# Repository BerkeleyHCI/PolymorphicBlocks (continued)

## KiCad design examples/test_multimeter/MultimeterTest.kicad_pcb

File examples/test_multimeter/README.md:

## Revision 2

Some items were out of stock and substituted with pin compatible alternatives:

- NLAS4157 (analog switch)
  - ~TS5A3160DCKR~
  - PI5A3157 (low-end), TS5A3159 (higher-end)
- TPA2005D1 (class D audio amp)
  - ~TPA2005D1DRBQ1 (8SON / DFN package)~ also out of stock =()
  - PAM8302AASCR (note internal resistors)
- TLV9061SQDBVRQ1 (opamp)
  - ~OPA991SIDBVR~ - NOT COMPATIBLE - IT'S ACTIVE HIGH SHUTDOWN

Part selection for some generics:
- Tactile switch
  - PTS820 J25K SMTR LFS
- FFC connector alternatives that are less expensive
  - 1734592-8
  - SFV8R-1STBE1HLF

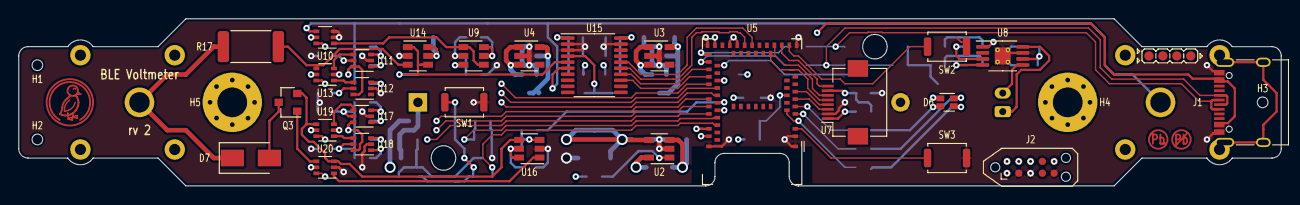
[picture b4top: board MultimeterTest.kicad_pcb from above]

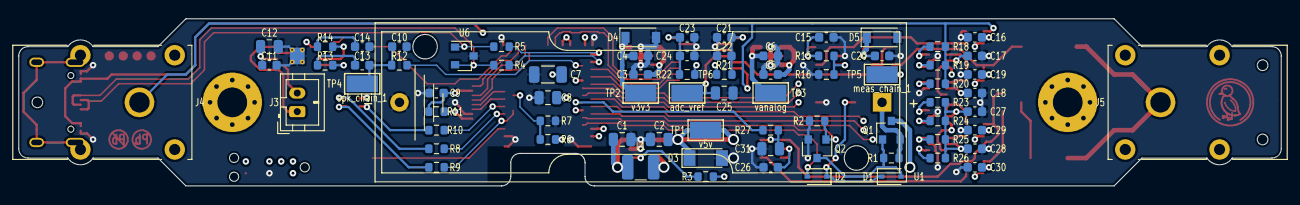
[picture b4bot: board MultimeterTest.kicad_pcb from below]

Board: 4 copper layers, 136.0 x 18.0 mm, 111 parts (76 on the bottom side), 80 nets.

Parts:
1: LeadFree; Indicator_LeadFree
2: IdDots4; Indicator_IdDots_4
C1, C8, C25: X5R 25V ±10% 10uF 0805 Multilayer Ceramic Capacit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; C_0805_2012Metric
C2, C12: 25V 4.7uF X5R ±10% 0805 Multilayer Ceramic Capaci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; C_0805_2012Metric
C3, C4, C5, C6, C9, C13, C14: 50V 1uF X5R ±10% 0603 Multilayer Ceramic Capacito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; C_0603_1608Metric
C7: 50V 10uF X5R ±10% 1206 Multilayer Ceramic Capacit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; C_1206_3216Metric
C10: 50V 47nF X7R ±10% 0603 Multilayer Ceramic Capacit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; C_0603_1608Metric
C11, C15, C16, C17, C18, C19, C20, C21, C22, C23, C24, C26, C27, C28, C29, C30: 50V 100nF X7R ±10% 0603 Multilayer Ceramic Capaci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; C_0603_1608Metric
C31: 50V 2.2uF Y5V ±20% 0805 Multilayer Ceramic Capaci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; C_0805_2012Metric
D1, D2: 30V 370mV@1mA 30mA SOD-323 Schottky Barrier Diode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; D_SOD-323
D3: 100nA@1V 25Ω Single 5.2V~6V 500mW 5.6V LL-34 Zene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; D_MiniMELF
D4, D5: 5μA@1V 90Ω Single 3.6V~3.8V 350mW 3.4V SOD-123 Ze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; D_SOD-123
D6: LED_LiteOn_LTST-C19HE1WT
D7: DIODE GEN PURP 400V 1A DO214AC; D_SMA
H1, H2, H3: JlcToolingHole_1.152mm
H4, H5: M3; MountingHole_3.2mm_M3_Pad_Via
J1: USB_C_Receptacle_XKB_U262-16XN-4BVC11
J2: SWD; Tag-Connect_TC2050-IDC-NL_2x05_P1.27mm_Vertical
J3: JST_PH_B2B-PH-K_1x02_P2.00mm_Vertical
J4, J5: CLIFF_FCR7350
L1: 620mA 22uH ±10% 270mΩ 1210 Inductors (SMD) ROHS; L_1210_3225Metric
Q1: 20V 3.1A 860mW 112mΩ@4.5V,2.8A 1V@250μA P Channel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; SOT-23
Q2: 60V 115mA 200mW 7.5Ω@10V,500mA 2.5V@250μA N Chann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; SOT-23
Q3: MOSFET P-CH 250V 140MA SC-59-3; SOT-23
R1, R2, R3, R6, R7, R8, R9, R10, R12, R13, R14, R15, R16, R18, R19, R20, R23, R24, R25, R26, R27: ±1% 1/10W Thick Film Resistors 75V ±100ppm/℃ -55℃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; R_0603_1608Metric
R4, R5, R11: ±1% 1/10W Thick Film Resistors 75V ±200ppm/℃ -55℃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; R_0603_1608Metric
R17: 1M, 1%, 1.0 W; R_2512_6332Metric
R21, R22: ±1% 1/10W Thick Film Resistors 75V ±400ppm/℃ -55℃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; R_0603_1608Metric
SW1, SW2, SW3: SW_Push_SPST_NO_Alps_SKRK
TP1: v5v; TestPoint_Keystone_5015_Micro-Minature
TP2: v3v3; TestPoint_Keystone_5015_Micro-Minature
TP3: vanalog; TestPoint_Keystone_5015_Micro-Minature
TP4: spk_chain_1; TestPoint_Keystone_5015_Micro-Minature
TP5: meas_chain_1; TestPoint_Keystone_5015_Micro-Minature
TP6: adc_vref; TestPoint_Keystone_5015_Micro-Minature
U1: BatteryHolder_Keystone_2460_1xAA
U2, U3, U4: SOT-23-5
U5: Raytac_MDBT50Q
U6: SOT-23
U7: Hirose_FH12-8S-0.5SH_1x08-1MP_P0.50mm_Horizontal
U8: MSOP-8-1EP_3x3mm_P0.65mm_EP1.73x1.85mm_ThermalVias
U9, U14, U16: SOT-23-6
U10, U11, U12, U13, U17, U18, U19, U20: SOT-363_SC-70-6
U15: TSSOP-20_4.4x6.5mm_P0.65mm
U21: Duck; Symbol_Duckling

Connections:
(adapter)inp.port.src: D7.1, J5.1, R17.1
adc.dvdd_res.b: C23.1, C24.1, R22.2, U15.20
adc.ic.avdd: C21.1, C22.1, R21.2, U15.1
adc.spi.miso: U5.24, U15.16
adc.spi.mosi: U5.26, U15.15
adc.spi.sck: U5.37, U15.14
adc_vref: C25.1, TP6.1, U15.4
data_usb.A4: C7.1, J1.A4, J1.A9, J1.B4, J1.B9, U5.32
data_usb.usb.dm: J1.A7, J1.B7, R5.2, U6.1
data_usb.usb.dp: J1.A6, J1.B6, R4.2, U6.2
driver.control: C31.1, R27.2, U16.3
driver.fet.drain: D7.2, Q3.3
driver.range.switch.inputs.0: R23.2, U17.3
driver.range.switch.inputs.1: R24.2, U17.1
driver.range.switch.inputs.2: R25.2, U18.3
driver.range.switch.inputs.3: R26.2, U18.1
driver.range.switch.sw[1_0].inputs.0: U17.4, U19.3
driver.range.switch.sw[1_0].inputs.1: U18.4, U19.1
driver.select.0_0: U5.46, U17.6, U18.6
driver.sw.inputs.0: Q3.2, U16.4, U19.4, U20.3
driver.sw.inputs.1: U16.1, U20.1
driver.sw.out: Q3.1, U20.4
gate.amp_fet.drain: D1.2, Q1.1, Q2.3, R1.2
gate.ctl_diode.cathode: D1.1, D2.1, SW1.2
gate.pwr_out: C1.1, L1.1, Q1.3, R3.1, R6.1, U2.3
gnd: C1.2, C2.2, C3.2, C4.2, C5.2, C6.2, C7.2, C8.2, C9.2, C10.2, C11.2, C12.2, C14.2, C15.2, C16.2, C17.2, C18.2, C19.2, C20.2, C21.2, C22.2, C23.2, C24.2, C25.2, C26.2, C27.2, C28.2, C29.2, C30.2, C31.2, D3.2, D4.2, D5.2, J1.A1, J1.A12, J1.B1, J1.B12, J2.2, J2.3, J2.5, Q2.2, R2.2, R7.2, R16.2, SW1.1, SW2.1, SW3.1, U1.2, U2.2, U3.2, U4.2, U5.1, U5.2, U5.15, U5.33, U5.55, U6.3, U7.2, U8.7, U8.9, U9.2, U10.2, U10.3, U11.2, U12.2, U13.2, U14.2, U15.2, U15.3, U15.19, U16.2, U17.2, U18.2, U19.2, U20.2
inn_merge.inputs.0: J4.1, R18.1, R19.1, R20.1, U10.4, U15.6
inn_mux.control.0: U5.41, U10.6
lcd.led_res.b: R11.2, U7.1
lcd.spi.mosi: U5.19, U7.5
lcd.spi.sck: U5.18, U7.6
mcu.adc.vbatsense: R6.2, R7.1, U5.9
mcu.gpio.adc_cs: U5.39, U15.13
mcu.gpio.driver_control: R27.1, U5.45
mcu.gpio.driver_enable: U5.48, U20.6
mcu.gpio.driver_select_1_0: U5.44, U19.6
mcu.gpio.gate_control: Q2.1, R2.1, U5.49
mcu.gpio.lcd_cs: U5.17, U7.8
mcu.gpio.lcd_reset: U5.8, U7.3
mcu.gpio.lcd_rs: U5.10, U7.4
mcu.gpio.measure_select_0_0: U5.42, U11.6, U12.6
mcu.gpio.measure_select_1_0: U5.43, U13.6
mcu.gpio.rgb_blue: R10.2, U5.6
mcu.gpio.sw0: D2.2, U5.50
mcu.gpio.sw1: SW2.2, U5.16
mcu.gpio.sw2: SW3.2, U5.3
mcu.ic.swd.reset: J2.6, U5.40
mcu.ic.swd.swdio: J2.10, U5.51
mcu.swd.swd.swclk: J2.9, U5.53
mcu.swd.swd.swo: J2.8, U5.47
mcu.usb_res.usb_inner.dm: R5.1, U5.34
mcu.usb_res.usb_inner.dp: R4.1, U5.35
meas_chain_0: R17.2, U13.4, U14.3
meas_chain_1: TP5.1, U14.1, U14.4, U15.5
measure.range.switch.inputs.0: R18.2, U11.3
measure.range.switch.inputs.1: R19.2, U11.1
measure.range.switch.inputs.2: R20.2, U12.3
measure.range.switch.sw[1_0].inputs.0: U11.4, U13.3
measure.range.switch.sw[1_0].inputs.1: U12.4, U13.1
ref_buf.inp: R15.2, R16.1, U9.3
reg_5v.ic.ce: R3.2, U2.1
reg_5v.power_path.switch: L1.2, U2.5
rgb.blue_res.a: D6.1, R10.1
rgb.green_res.a: D6.4, R9.1
rgb.red_res.a: D6.3, R8.1
rgb.signals.green: R9.2, U5.5
rgb.signals.red: R8.2, U5.4
spk_chain_0: R12.1, U5.36
spk_chain_1: C10.1, C13.2, R12.2, TP4.1
spk_chain_2.a: J3.1, U8.8
spk_chain_2.b: J3.2, U8.5
spk_drv.(adapter)inp_res.b.dst: R13.2, U8.4
spk_drv.ic.inn: R14.2, U8.3
spk_drv.inn_res.a: C14.1, R14.1
spk_drv.inp_res.a: C13.1, R13.1
v3v3: C4.1, C8.1, C9.1, D4.1, D6.2, J2.1, R11.1, R22.1, TP2.1, U3.5, U5.28, U5.30, U7.7
v5v: C2.1, C3.1, C5.1, C11.1, C12.1, D3.1, TP1.1, U2.4, U3.1, U3.3, U4.1, U4.3, U8.1, U8.6
vanalog: C6.1, C15.1, C16.1, C17.1, C18.1, C19.1, C20.1, C26.1, C27.1, C28.1, C29.1, C30.1, D5.1, R15.1, R21.1, R23.1, R24.1, R25.1, R26.1, TP3.1, U4.5, U9.5, U9.6, U10.5, U11.5, U12.5, U13.5, U14.5, U14.6, U16.5, U16.6, U17.5, U18.5, U19.5, U20.5
vbat: Q1.2, R1.1, U1.1
vcenter: U9.1, U9.4, U10.1

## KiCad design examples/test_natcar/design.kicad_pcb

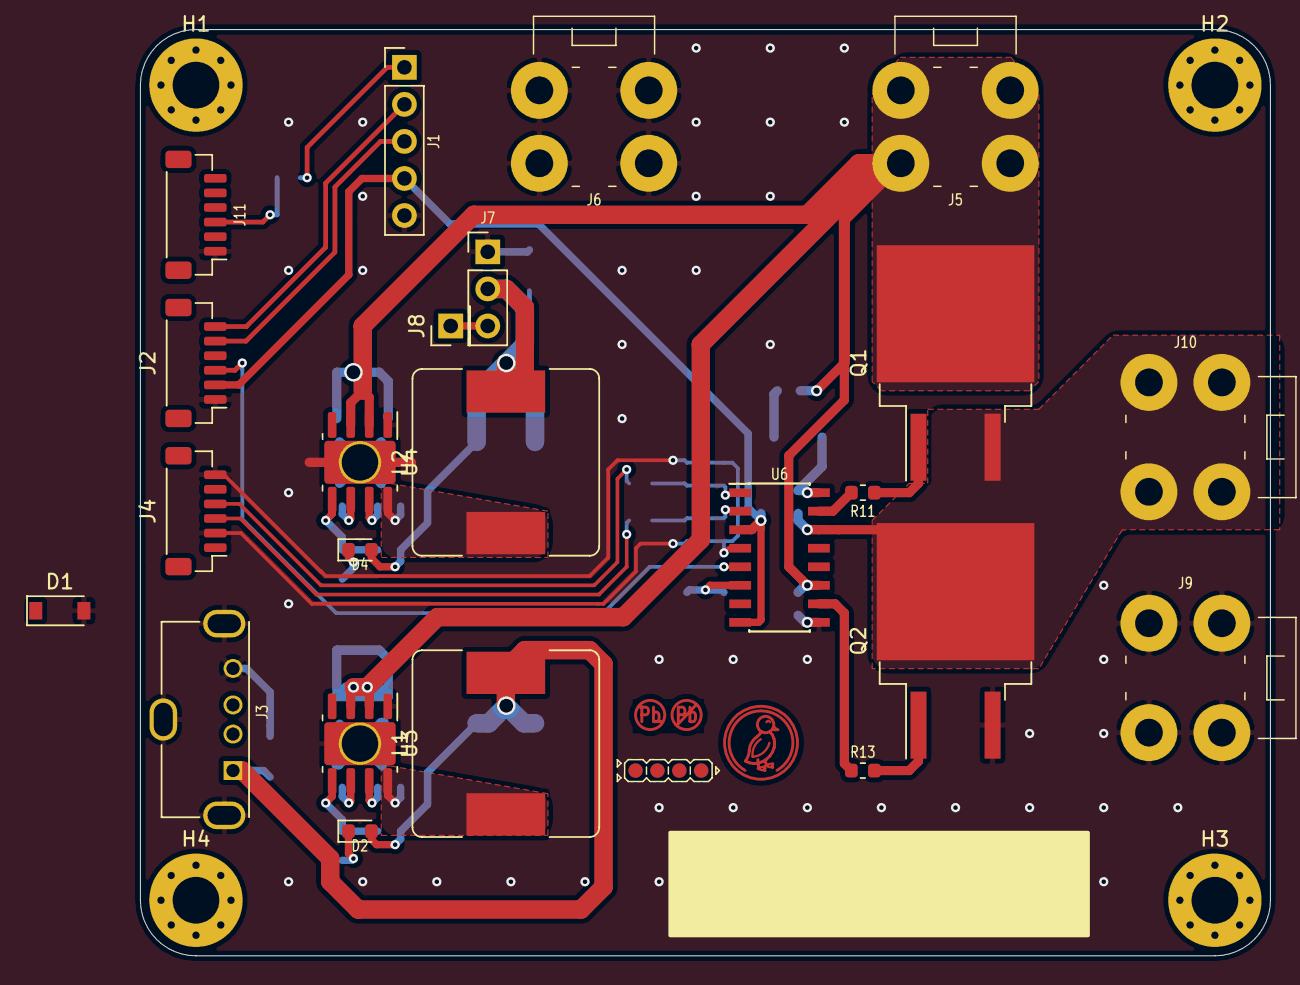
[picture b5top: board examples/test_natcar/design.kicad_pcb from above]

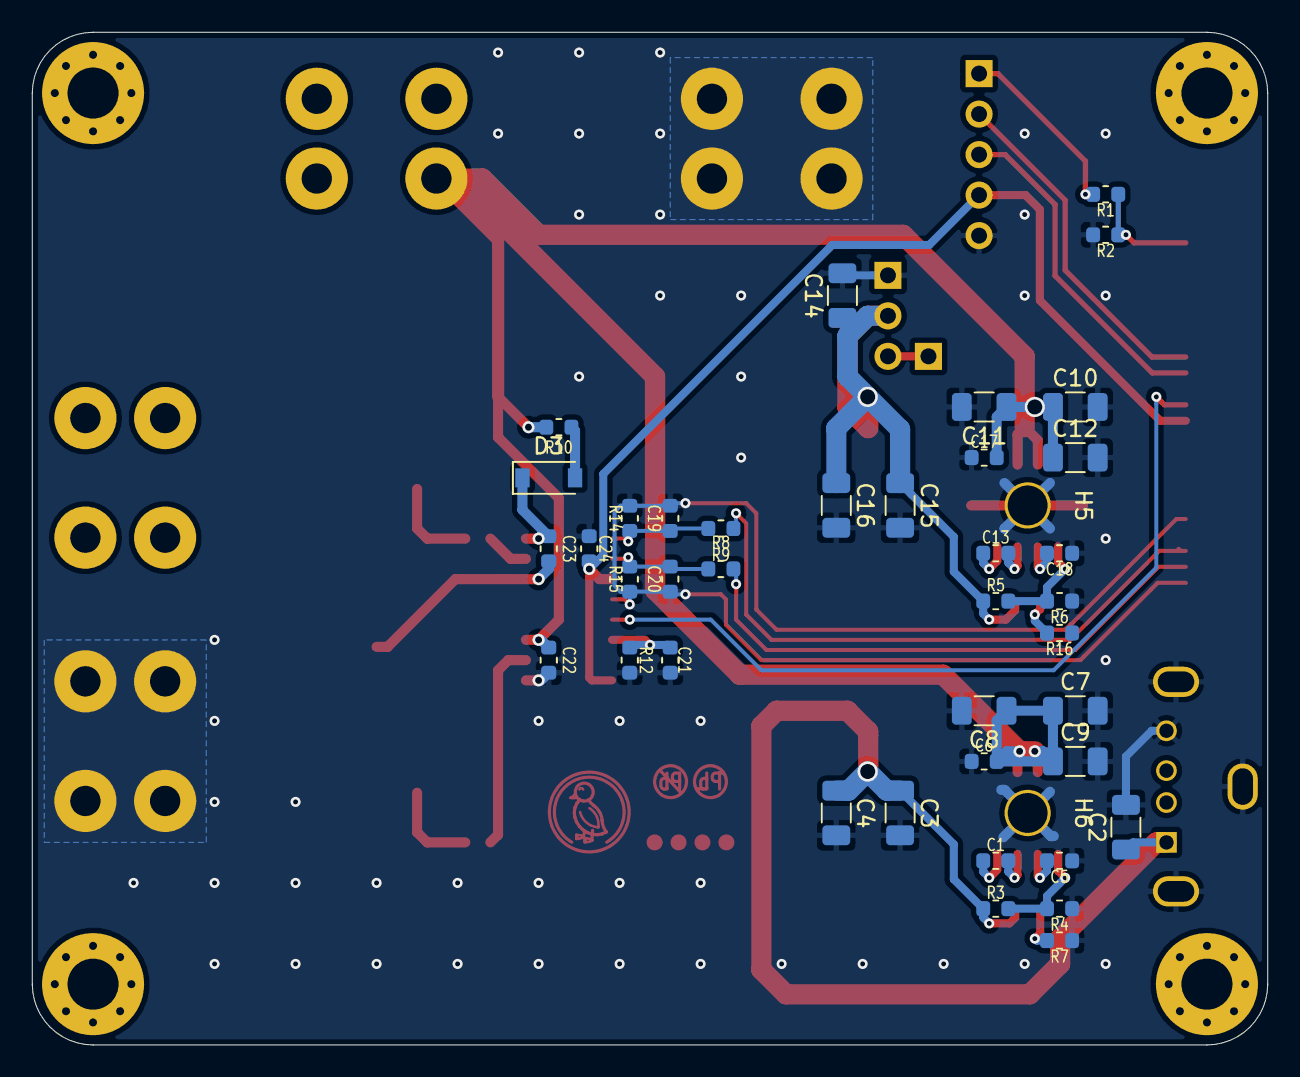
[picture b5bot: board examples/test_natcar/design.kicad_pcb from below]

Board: 2 copper layers, 77.5 x 63.5 mm, 71 parts (41 on the bottom side), 33 nets.

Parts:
C1, C13, C24: 0.1µF, 50V, CL10B104KB8NNNC; C_0603_1608Metric
C2, C3, C4: 10µF, 6.3V, CL31A106MQHNNNE; C_1206_3216Metric
C5, C18, C22, C23: 1µF, 25V, CL10A105KA8NNNC; C_0603_1608Metric
C6, C17: 0.22µF, 16V, CL10B224KO8NNNC; C_0603_1608Metric
C7, C8, C9, C10, C11, C12, C14, C15, C16: 10µF, 25V, CL31A106KAHNNNE; C_1206_3216Metric
C19, C20: 100pF, 50V, CL10C101JB8NNNC; C_0603_1608Metric
C21: 2200pF, 50V, CL10B222JB8NNNC; C_0603_1608Metric
D1: MMSZ5245B-TP; D_SOD-123
D2, D4: LED_0603_1608Metric
D3: CRS01(TE85L,Q,M); D_SOD-123
H1, H2, H3, H4: M3; MountingHole_3.2mm_M3_Pad_Via
H5, H6: M2.5; MountingHole_2.5mm
J1: Header 5-pos; PinHeader_1x05_P2.54mm_Vertical
J2, J4, J11: JST-SH 6-pos; JST_SH_BM06B-SRSS-TB_1x06-1MP_P1.00mm_Vertical
J3: Molex 105057; USB_A_Molex_105057_Vertical
J5, J6, J9, J10: PLACEHOLDER_M3ScrewTerminal; ScrewTerminal_M3_RA_Keystone7761
J7: Header 3-pos; PinHeader_1x03_P2.54mm_Vertical
J8: Header 1-pos; PinHeader_1x01_P2.54mm_Vertical
L1, L2: 10µH, 5.5A, SRR1260-100M; L_Bourns_SRR1260
Q1, Q2: PSMN4R3-30BL,118; TO-263-2
R1, R12: 22k, 1%, 0.1W; R_0603_1608Metric
R2: 18k, 1%, 0.1W; R_0603_1608Metric
R3, R5: 330k, 1%, 0.1W; R_0603_1608Metric
R4: 82k, 1%, 0.1W; R_0603_1608Metric
R6: 68k, 1%, 0.1W; R_0603_1608Metric
R7, R16: 1k, 1%, 0.1W; R_0603_1608Metric
R8, R9: 150, 1%, 0.1W; R_0603_1608Metric
R10, R11, R13: 2.2, 1%, 0.1W; R_0603_1608Metric
R14, R15: 10k, 1%, 0.1W; R_0603_1608Metric
U1: LeadFree; Indicator_LeadFree
U2: Duck; Symbol_Duckling
U3, U4: LMR33630; SOIC-8-1EP_3.9x4.9mm_P1.27mm_EP2.95x4.9mm_Mask2.71x3.4mm
U5: IdDots4; Indicator_IdDots_4
U6: UCC21222; SOIC-16_3.9x9.9mm_P1.27mm

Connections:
C1.1: C1.1, U3.7
C1.2: C1.2, L1.1, U3.8
C13.1: C13.1, U4.7
C18.1: C18.1, U4.6
D2.1: D2.1, R7.1
D3.2: D3.2, R10.2
L2.1: C13.2, L2.1, U4.8
R4.1: R3.2, R4.1, U3.5
R8.2: C19.1, R8.2, R14.2, U6.1
R11.2: Q1.1, R11.2
R12.1: C21.1, R12.1, U6.6
R13.1: R13.1, U6.10
R13.2: Q2.1, R13.2
R16.1: D4.1, R16.1
U3.6: C5.1, U3.6
U4.5: R5.2, R6.1, U4.5
U6.2: C20.1, R9.2, R15.2, U6.2
U6.15: R11.1, U6.15
U6.16: C23.1, D3.1, U6.16
cam_conn.clk: J1.3, J2.5
cam_conn.si: J1.2, J2.6
cam_div.output: J11.3, R1.2, R2.1
cam_div.top: J1.1, R1.1
drv1.ina: J4.4, R8.1
drv1.pwr: C24.1, J1.4, J2.2, U6.3, U6.8
gnd: C2.2, C3.2, C4.2, C5.2, C6.2, C7.2, C8.2, C9.2, C10.2, C11.2, C12.2, C14.2, C15.2, C16.2, C17.2, C18.2, C19.2, C20.2, C21.2, C22.2, C24.2, D1.2, H5.1, H6.1, J1.5, J2.1, J3.4, J3.5, J4.2, J4.6, J6.1, J7.1, J9.1, J11.1, Q2.3, R2.2, R4.2, R6.2, R7.2, R12.2, R14.1, R15.1, R16.2, U3.1, U3.9, U4.1, U4.9, U6.4, U6.9
gpio_conn.gp0: J2.3, U6.5
motor.a: C23.2, J10.1, Q1.3, Q2.2, U6.14
pwm_conn.pwm0: J4.3, R9.1
srv.sig: J7.3, J8.1
vin: C6.1, C7.1, C8.1, C9.1, C10.1, C11.1, C12.1, C17.1, C22.1, D1.1, J5.1, Q1.2, R10.1, U3.2, U3.3, U4.2, U4.3, U6.11
vsrv: C14.1, C15.1, C16.1, D4.2, J7.2, L2.2, R5.1
vusb: C2.1, C3.1, C4.1, D2.2, J3.1, L1.2, R3.1

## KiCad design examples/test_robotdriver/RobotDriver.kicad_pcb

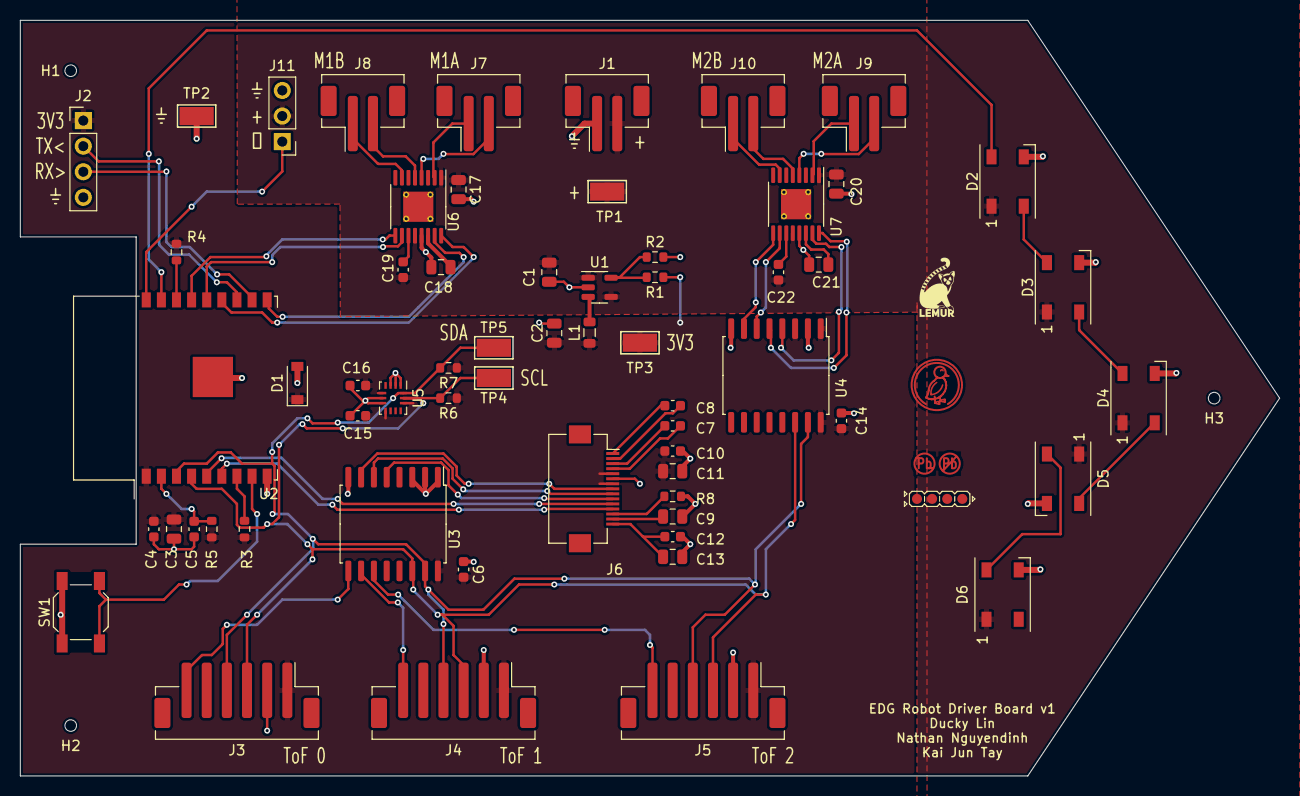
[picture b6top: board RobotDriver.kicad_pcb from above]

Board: 2 copper layers, 125.0 x 75.0 mm, 68 parts (0 on the bottom side), 54 nets.

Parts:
1: Indicator_LeadFree
2: Indicator_IdDots_4
C1, C2, C9, C11, C18, C21: C1779; C_0805_2012Metric
C3, C13, C17, C20: C15850; C_0805_2012Metric
C4, C6, C7, C8, C10, C12, C14, C15, C16: C14663; C_0603_1608Metric
C5: C15849; C_0603_1608Metric
C19, C22: C57112; C_0603_1608Metric
D1: C499796; D_SOD-123
D2, D3, D4, D5, D6: C2920042; LED_WS2812B_PLCC4_5.0x5.0mm_P3.2mm
H1, H2, H3: JlcToolingHole_1.152mm
J1, J7, J8, J9, J10: C64658; JST_PH_B2B-PH-SM4-TB_1x02-1MP_P2.00mm_Vertical
J2: PinHeader_1x04_P2.54mm_Vertical
J3, J4, J5: C265088; JST_PH_B6B-PH-SM4-TB_1x06-1MP_P2.00mm_Vertical
J6: Hirose_FH12-15S-0.5SH_1x15-1MP_P0.50mm_Horizontal
J11: PinHeader_1x03_P2.54mm_Vertical
L1: C98331; L_0805_2012Metric
R1: C23231; R_0603_1608Metric
R2: C22809; R_0603_1608Metric
R3, R4, R5: C25804; R_0603_1608Metric
R6, R7: C23162; R_0603_1608Metric
R8: C23203; R_0603_1608Metric
SW1: C318884; SW_SPST_SKQG_WithoutStem
TP1, TP2, TP3, TP4, TP5: C238130; TestPoint_Keystone_5015_Micro-Minature
U1: C500769; SOT-23-5
U2: C2934560; ESP-WROOM-02
U3, U4: C86832; SOIC-16W_7.5x10.3mm_P1.27mm
U5: C967633; Bosch_LGA-14_3x2.5mm_P0.5mm
U6, U7: C50506; TSSOP-16-1EP_4.4x5mm_P0.65mm_EP3x3mm_ThermalVias
U8: Symbol_LemurSmall
U9: Symbol_Duckling

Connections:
expander.io.lcd_cs: J6.8, U3.7
expander.io.lcd_dc: J6.10, U3.5
expander.io.lcd_reset: J6.9, U3.6
expander.io.tof_xshut_0: J3.6, U3.9
gnd: C1.2, C2.2, C3.2, C4.2, C5.2, C6.2, C9.2, C10.2, C11.2, C12.2, C13.2, C14.2, C15.2, C16.2, C17.2, C18.2, C20.2, C21.2, D1.2, D2.3, D3.3, D4.3, D5.3, D6.3, J1.1, J2.4, J3.2, J4.2, J5.2, J6.6, J11.3, R2.2, R8.2, SW1.1, TP2.1, U1.2, U2.9, U2.19, U3.1, U3.2, U3.3, U3.8, U4.2, U4.8, U5.1, U5.2, U5.3, U5.6, U5.7, U6.13, U6.17, U7.13, U7.17
i2c_chain_0.scl: J3.3, J4.3, J5.3, R6.2, TP4.1, U2.4, U3.14, U4.14, U5.13
i2c_chain_0.sda: J3.4, J4.4, J5.4, R7.2, TP5.1, U2.3, U3.15, U4.15, U5.14
lcd.c1_cap.neg: C7.2, J6.4
lcd.c1_cap.pos: C7.1, J6.3
lcd.c2_cap.neg: C8.2, J6.2
lcd.c2_cap.pos: C8.1, J6.1
lcd.device.iref: J6.13, R8.1
lcd.spi.mosi: J6.12, U2.6
lcd.spi.sck: J6.11, U2.5
lcd.vcc_cap1.pos: C12.1, C13.1, J6.15
lcd.vcomh_cap.pwr: C9.1, J6.14
m1_a.pins.1: J7.1, U6.2
m1_a.pins.2: J7.2, U6.4
m1_b.pins.1: J8.1, U6.7
m1_b.pins.2: J8.2, U6.5
m2_a.pins.1: J9.1, U7.2
m2_a.pins.2: J9.2, U7.4
m2_b.pins.1: J10.1, U7.7
m2_b.pins.2: J10.2, U7.5
mcu.gpio.ledArray: D2.4, U2.17
mcu.gpio.motor_ain1: U2.13, U6.16
mcu.gpio.motor_ain2: U2.10, U6.15
mcu.gpio.motor_bin1: U2.15, U6.9
mcu.gpio.motor_bin2: U2.14, U6.10
mcu.ic.en: C5.1, R5.2, U2.2
mcu.ic.io8: R3.2, U2.7
mcu.io2_pull.io: R4.2, U2.16
mcu.prog.a: SW1.2, U2.8
mcu.uart0.pins.2: J2.2, U2.12
mcu.uart0.uart.tx: J2.3, U2.11
motor_driver1.vcp_cap.pos: C19.1, U6.11
motor_driver1.vint_cap.pwr: C18.1, U6.14
motor_driver2.vcp_cap.pos: C22.1, U7.11
motor_driver2.vint_cap.pos: C21.1, U7.14
motor_expander.io.motor_ain1: U4.5, U7.16
motor_expander.io.motor_ain2: U4.4, U7.15
motor_expander.io.motor_bin1: U4.7, U7.9
motor_expander.io.motor_bin2: U4.6, U7.10
reg_3v3.fb.center: R1.2, R2.1, U1.5
reg_3v3.power_path.switch: L1.1, U1.3
servo.pins.1: J11.1, U2.18
tof.xshut.1: J4.6, U3.10
tof.xshut.2: J5.6, U3.11
v3v3: C2.1, C3.1, C4.1, C6.1, C10.1, C11.1, C14.1, C15.1, C16.1, D1.1, J2.1, J3.1, J4.1, J5.1, J6.5, J6.7, L1.2, R1.1, R3.1, R4.1, R5.1, R6.1, R7.1, TP3.1, U2.1, U3.16, U4.1, U4.3, U4.16, U5.5, U5.8, U5.12
vbatt: C1.1, C17.1, C19.2, C20.1, C22.2, D2.1, D3.1, D4.1, D5.1, D6.1, J1.2, J11.2, TP1.1, U1.1, U1.4, U6.1, U6.12, U7.1, U7.12
ws2812bArray.led[0].dout: D2.2, D3.4
ws2812bArray.led[1].dout: D3.2, D4.4
ws2812bArray.led[3].din: D4.2, D5.4
ws2812bArray.led[3].dout: D5.2, D6.4
